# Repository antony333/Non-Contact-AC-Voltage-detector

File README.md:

# Non-Contact-AC-Voltage-detector
The objective of this project is to create a non-contact AC voltage detector on a PCB board.

https://user-images.githubusercontent.com/72541715/128242127-0ad2d9b1-51a4-4d22-9144-a7d4ea4d7757.mp4

## Softwares Used
**LT Spice  
KiCad** 

## Components
**NPN Transistor  
Resistor  
LED  
Buzzer  
Antenna  
Battery**

## Processes Involved
The circuit was initially simulated on LT Spice and the PCB layout was designed using KiCad. Drilling and etching processes were carried out manually.

## Working
The principle behind this device is electromagnetic induction. A magnetic field is produced around a current-carrying conductor and if the current through the conductor is AC the magnetic field produced varies periodically. When we place an antenna near an AC energised object, a small current gets induced in the antenna and activates the first transistor. The output of the 1st transistor drives the 2nd transistor, it gets activated, and so on. As the 3rd transistor is activated LED is turned ON and the buzzer starts beeping indicating the presence of AC Voltage.

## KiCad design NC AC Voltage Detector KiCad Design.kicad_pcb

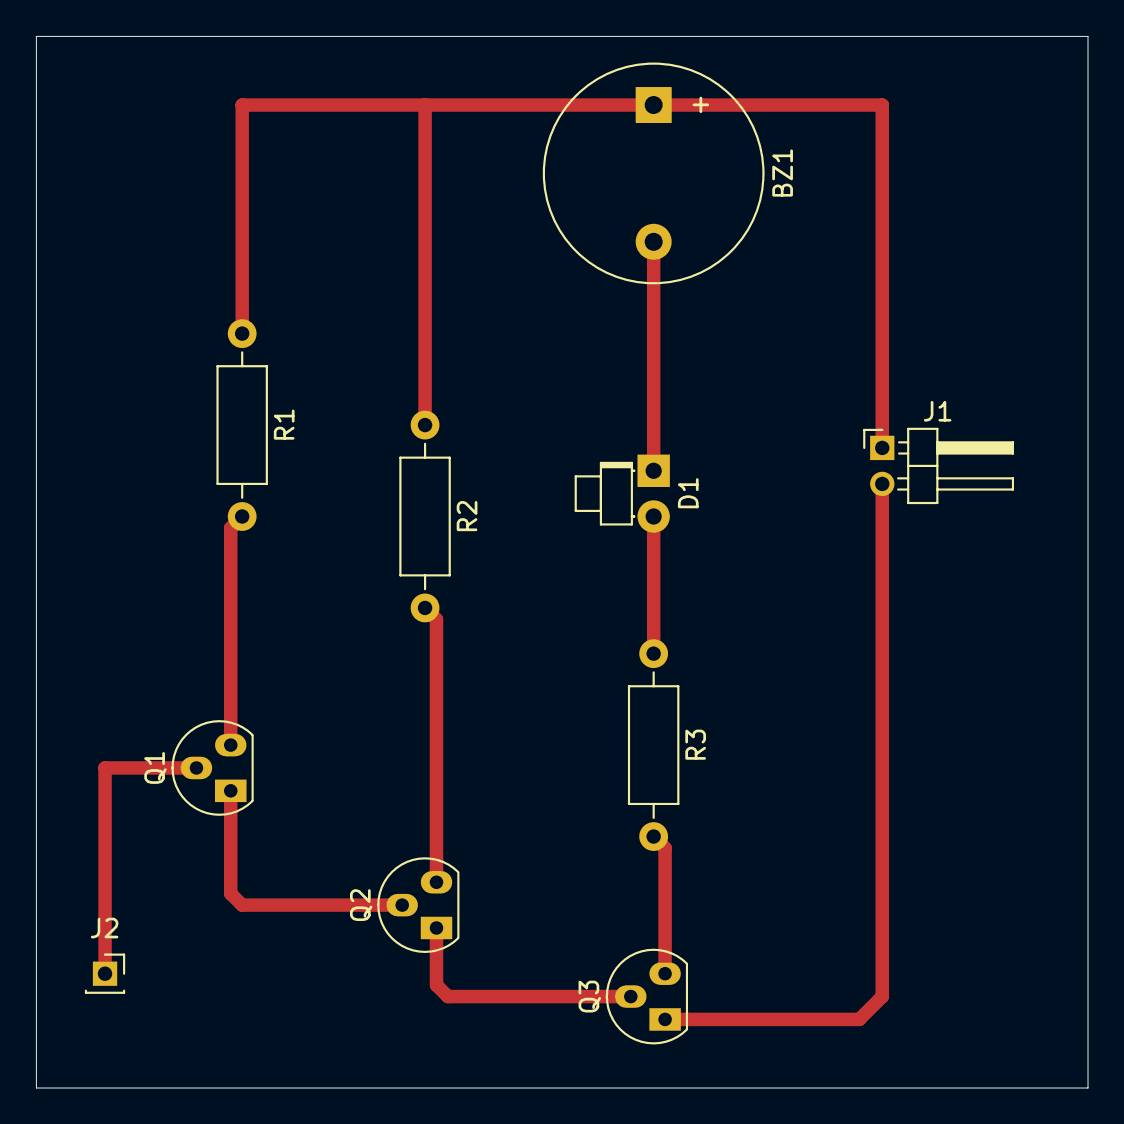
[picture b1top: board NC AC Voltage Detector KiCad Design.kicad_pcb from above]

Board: 2 copper layers, 58.4 x 58.4 mm, 10 parts (0 on the bottom side), 10 nets.

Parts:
BZ1: Buzzer; Buzzer_12x9.5RM7.6
D1: LED; LED_D1.8mm_W1.8mm_H2.4mm_Horizontal_O1.27mm_Z8.2mm
J1: Battery input; PinHeader_1x02_P2.00mm_Horizontal
J2: Conn_01x01_Female; PinSocket_1x01_P2.00mm_Vertical
Q1, Q2, Q3: 2N3904; TO-92_Inline
R1: 1 Meg; R_Axial_DIN0207_L6.3mm_D2.5mm_P10.16mm_Horizontal
R2: 100k; R_Axial_DIN0207_L6.3mm_D2.5mm_P10.16mm_Horizontal
R3: 220; R_Axial_DIN0207_L6.3mm_D2.5mm_P10.16mm_Horizontal

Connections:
+9V: BZ1.1, J1.1, R1.1, R2.1
GND: J1.2, Q3.1
unnamed: BZ1.2, D1.1
unnamed: D1.2, R3.1
unnamed: J2.1, Q1.2
unnamed: Q1.1, Q2.2
unnamed: Q1.3, R1.2
unnamed: Q2.1, Q3.2
unnamed: Q2.3, R2.2
unnamed: Q3.3, R3.2
